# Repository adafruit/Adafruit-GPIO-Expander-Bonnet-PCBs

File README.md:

## Adafruit GPIO Expander Bonnet PCB

<a href="http://www.adafruit.com/products/4132"><br/>
Click here to purchase one from the Adafruit shop</a>

PCB files for the Adafruit GPIO Expander Bonnet. Format is EagleCAD schematic and board layout
* https://www.adafruit.com/product/4132

### Description

The Raspberry Pi is an amazing single board computer - and one of the best parts is that GPIO connector! 40 pins of digital goodness you can twiddle to control LEDs, sensors, buttons, radios, displays - just about any device you can imagine. This Adafruit GPIO Expander Bonnet will give you even more digital deliciousness - 16 more digital input/output pins are yours for any desire you have. The outputs are grouped into two 16-pin connectors that have a matching ground pin. You can set each pin to be a digital output (high or low) or as an input, with an internal pull-up if you like!

Simply pop the Bonnet on top of your Pi, the circuitry connects to the SDA/SCL I2C pins for control. The MCP23017 chip converts our Python commands to pin instructions.

When used as an output, each pin can supply up to 20mA (current clamped) - so you can drive LEDs directly. The datasheet recommends you keep the total current draw to under 125mA for the whole chip. We set up the expander chip for 5V logic by default (the I2C is level shifted so that's 3V logic). We did that so you can drive white, blue or green LEDs that sometimes aren't too happy with 3.3V logic. Or, you can cut/solder a jumper to change it to 3.3V logic.

When used as an input, you can set up a pull-up resistor so buttons and switches don't need extra resistors - just wire the pin to one side and ground to the other! There's interrupt capabilities on the chip, and two IRQ pins (INTA and INTB) you can solder a wire to, if you want to have a quick way of telling if any of the GPIO's changed.

By soldering close the address select jumpers, you can change the address from 0x20 up to 0x27. So, if you wanted to, you could have up to 8 bonnets for 128 total GPIO.

Comes as an assembled and tested Bonnet with slim 2x20 header connector on the bottom. We provide 2 sets of 16-pin IDC sockets, you can solder these in or leave them off for a slim setup. [Follow our guide to use our CircuitPython library with Python 3 for fast and easy setup and configuration, you'll be running in under 5 minutes.](https://learn.adafruit.com/gpio-expander-bonnet/overview)

<b>As of October 31, 2023</b> - We've added an on-board Stemma QT port for easy plug-n-play of I2C sensors and devices. The board also now comes with the two IDC socket headers pre-soldered. Lastly, we've also updated it with Adafruit Pinguin to make a lovely and legible silkscreen

### License

Adafruit invests time and resources providing this open source design, please support Adafruit and open-source hardware by purchasing products from [Adafruit](https://www.adafruit.com)!

Designed by Limor Fried/Ladyada for Adafruit Industries.

Creative Commons Attribution/Share-Alike, all text above must be included in any redistribution. See license.txt for additional details.

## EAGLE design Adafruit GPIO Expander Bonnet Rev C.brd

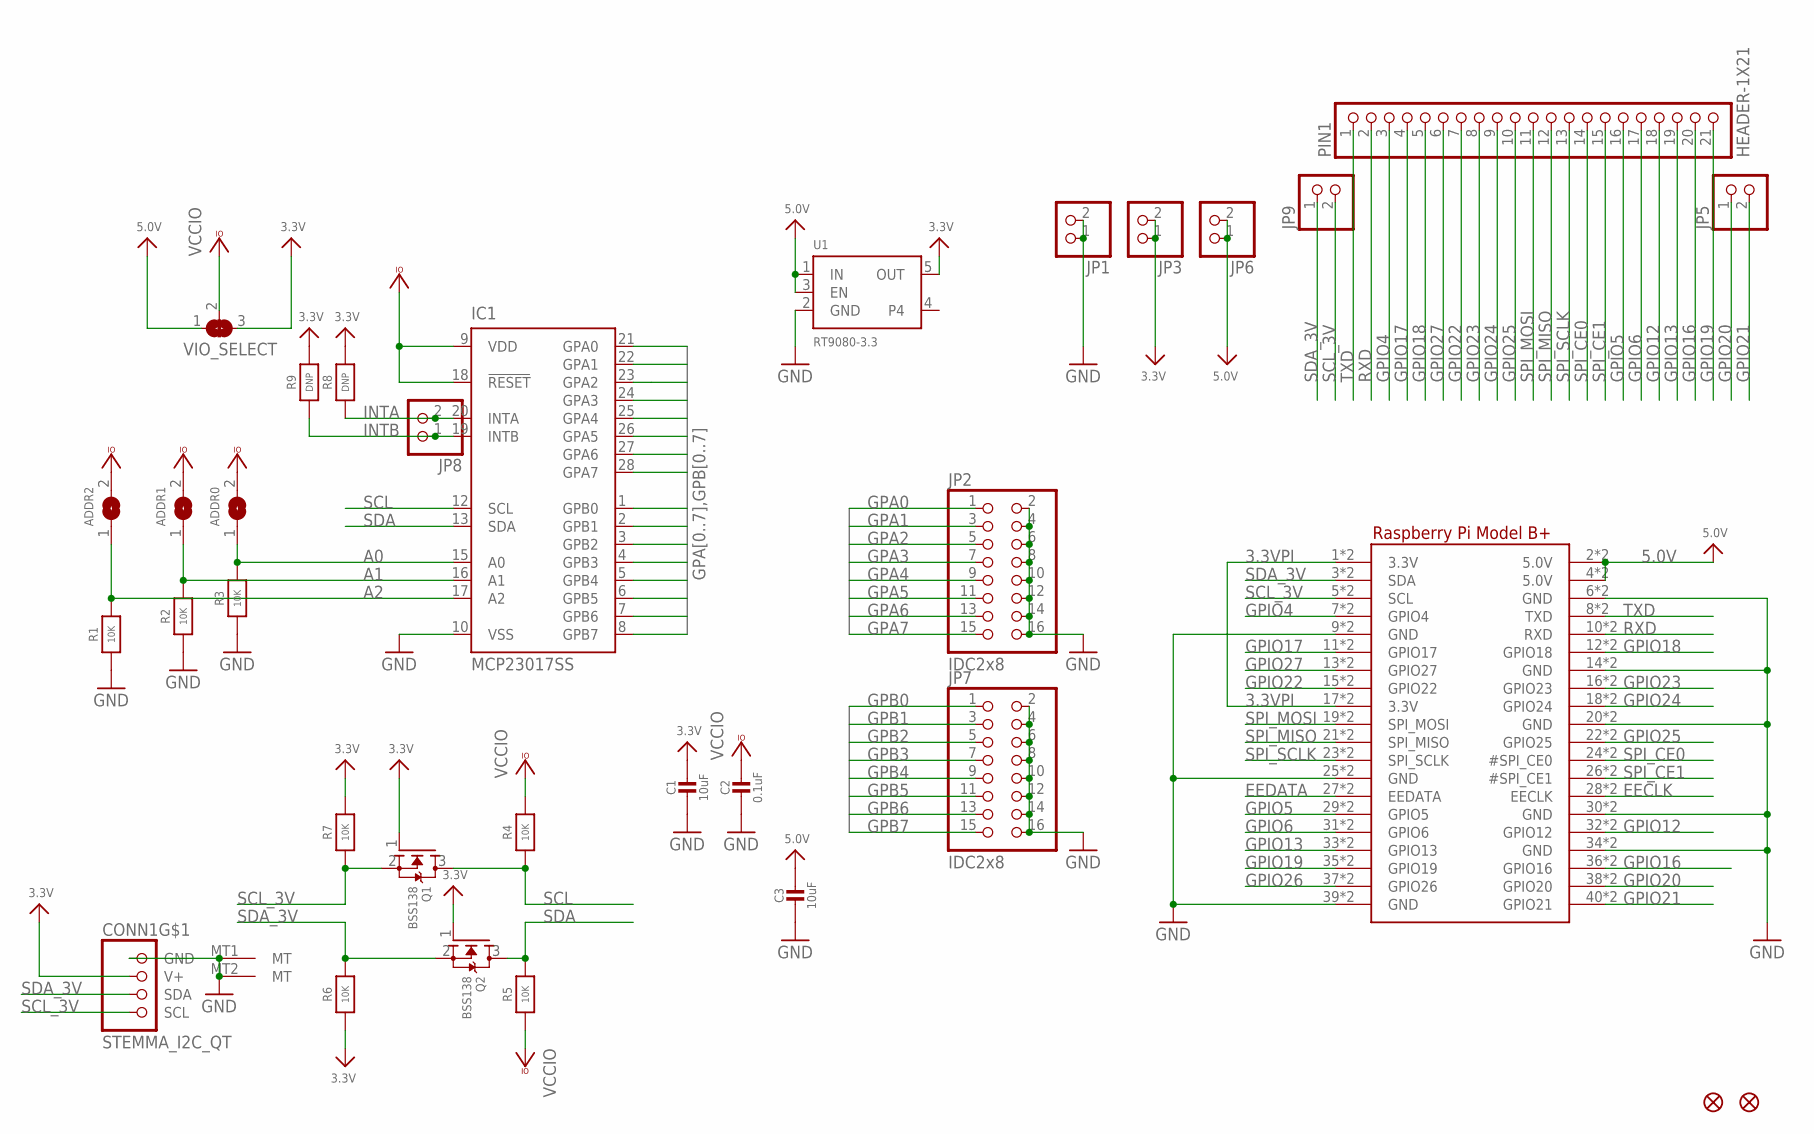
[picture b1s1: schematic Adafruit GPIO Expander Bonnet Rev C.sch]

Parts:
ADDR0, ADDR1, ADDR2: SOLDERJUMPER; SOLDERJUMPER_ARROW_NOPASTE
C1, C3: 10uF; 0805-NO
C2: 0.1uF; 0603-NO
CONN1: STEMMA_I2C_QT; JST_SH4
FID1, FID2: FIDUCIAL_1MM
IC1: MCP23017SS; SSOP28
JP1, JP3, JP5, JP6, JP8, JP9: HEADER-1X2ROUND; 1X02_ROUND
JP2, JP7: IDC2x8; 2X08_SHROUDED
PIN1: HEADER-1X21; 1X21_ROUND_70MIL
Q1, Q2: BSS138; SOT23-WIDE
R1, R2, R3, R4, R5, R6, R7: 10K; 0603-NO
R8, R9: DNP; 0603-NO
RPI1: RASPBERRYPI_BPLUS_BONNET_THMSMT; PI_BONNET_THMSMT
U1: RT9080-3.3; SOT23-5; JLC_ROTATION 0
VIO_SELECT: SOLDERJUMPER_2WAY; SOLDERJUMPER_2WAY_OPEN_NOPASTE

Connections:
3.3V: C1.1, CONN1.2 (V+), JP3.1, JP3.2, Q1.1 (G), Q2.1 (G), R6.1, R7.2, R8.2, R9.2, U1.5 (OUT), VIO_SELECT.3
3.3VPI: RPI1.1 (3.3V), RPI1.17 (3.3V), RPI1.S1 (3.3V), RPI1.S17 (3.3V)
5.0V: C3.1, JP6.1, JP6.2, RPI1.2 (5.0V), RPI1.4 (5.0V), RPI1.S2 (5.0V), RPI1.S4 (5.0V), U1.1 (IN), U1.3 (EN), VIO_SELECT.1
A0: ADDR0.1, IC1.15 (A0), R3.2
A1: ADDR1.1, IC1.16 (A1), R2.2
A2: ADDR2.1, IC1.17 (A2), R1.2
EECLK: RPI1.28 (EECLK), RPI1.S28 (EECLK)
EEDATA: RPI1.27 (EEDATA), RPI1.S27 (EEDATA)
GND: C1.2, C2.2, C3.2, CONN1.1 (GND), CONN1.MT1 (MT), CONN1.MT2 (MT), IC1.10 (VSS), JP1.1, JP1.2, JP2.2, JP2.4, JP2.6, JP2.8, JP2.10, JP2.12, JP2.14, JP2.16, JP7.2, JP7.4, JP7.6, JP7.8, JP7.10, JP7.12, JP7.14, JP7.16, R1.1, R2.1, R3.1, RPI1.6 (GND), RPI1.9 (GND), RPI1.14 (GND), RPI1.20 (GND), RPI1.25 (GND), RPI1.30 (GND), RPI1.34 (GND), RPI1.39 (GND), RPI1.S6 (GND), RPI1.S9 (GND), RPI1.S14 (GND), RPI1.S20 (GND), RPI1.S25 (GND), RPI1.S30 (GND), RPI1.S34 (GND), RPI1.S39 (GND), U1.2 (GND)
GPA0: IC1.21 (GPA0), JP2.1
GPA1: IC1.22 (GPA1), JP2.3
GPA2: IC1.23 (GPA2), JP2.5
GPA3: IC1.24 (GPA3), JP2.7
GPA4: IC1.25 (GPA4), JP2.9
GPA5: IC1.26 (GPA5), JP2.11
GPA6: IC1.27 (GPA6), JP2.13
GPA7: IC1.28 (GPA7), JP2.15
GPB0: IC1.1 (GPB0), JP7.1
GPB1: IC1.2 (GPB1), JP7.3
GPB2: IC1.3 (GPB2), JP7.5
GPB3: IC1.4 (GPB3), JP7.7
GPB4: IC1.5 (GPB4), JP7.9
GPB5: IC1.6 (GPB5), JP7.11
GPB6: IC1.7 (GPB6), JP7.13
GPB7: IC1.8 (GPB7), JP7.15
GPIO4: PIN1.3, RPI1.7 (GPIO4), RPI1.S7 (GPIO4)
GPIO5: PIN1.16, RPI1.29 (GPIO5), RPI1.S29 (GPIO5)
GPIO6: PIN1.17, RPI1.31 (GPIO6), RPI1.S31 (GPIO6)
GPIO12: PIN1.18, RPI1.32 (GPIO12), RPI1.S32 (GPIO12)
GPIO13: PIN1.19, RPI1.33 (GPIO13), RPI1.S33 (GPIO13)
GPIO16: PIN1.20, RPI1.36 (GPIO16), RPI1.S36 (GPIO16)
GPIO17: PIN1.4, RPI1.11 (GPIO17), RPI1.S11 (GPIO17)
GPIO18: PIN1.5, RPI1.12 (GPIO18), RPI1.S12 (GPIO18)
GPIO19: PIN1.21, RPI1.35 (GPIO19), RPI1.S35 (GPIO19)
GPIO20: JP5.1, RPI1.38 (GPIO20), RPI1.S38 (GPIO20)
GPIO21: JP5.2, RPI1.40 (GPIO21), RPI1.S40 (GPIO21)
GPIO22: PIN1.7, RPI1.15 (GPIO22), RPI1.S15 (GPIO22)
GPIO23: PIN1.8, RPI1.16 (GPIO23), RPI1.S16 (GPIO23)
GPIO24: PIN1.9, RPI1.18 (GPIO24), RPI1.S18 (GPIO24)
GPIO25: PIN1.10, RPI1.22 (GPIO25), RPI1.S22 (GPIO25)
GPIO26: RPI1.37 (GPIO26), RPI1.S37 (GPIO26)
GPIO27: PIN1.6, RPI1.13 (GPIO27), RPI1.S13 (GPIO27)
INTA: IC1.20 (INTA), JP8.2, R8.1
INTB: IC1.19 (INTB), JP8.1, R9.1
RXD: PIN1.2, RPI1.10 (RXD), RPI1.S10 (RXD)
SCL: IC1.12 (SCL), Q1.3 (D), R4.1
SCL_3V: CONN1.4 (SCL), JP9.2, Q1.2 (S), R7.1, RPI1.5 (SCL), RPI1.S5 (SCL)
SDA: IC1.13 (SDA), Q2.3 (D), R5.2
SDA_3V: CONN1.3 (SDA), JP9.1, Q2.2 (S), R6.2, RPI1.3 (SDA), RPI1.S3 (SDA)
SPI_CE0: PIN1.14, RPI1.24 (#SPI_CE0), RPI1.S24 (#SPI_CE0)
SPI_CE1: PIN1.15, RPI1.26 (#SPI_CE1), RPI1.S26 (#SPI_CE1)
SPI_MISO: PIN1.12, RPI1.21 (SPI_MISO), RPI1.S21 (SPI_MISO)
SPI_MOSI: PIN1.11, RPI1.19 (SPI_MOSI), RPI1.S19 (SPI_MOSI)
SPI_SCLK: PIN1.13, RPI1.23 (SPI_SCLK), RPI1.S23 (SPI_SCLK)
TXD: PIN1.1, RPI1.8 (TXD), RPI1.S8 (TXD)
VCCIO: ADDR0.2, ADDR1.2, ADDR2.2, C2.1, IC1.9 (VDD), IC1.18 (!RESET), R4.2, R5.1, VIO_SELECT.2

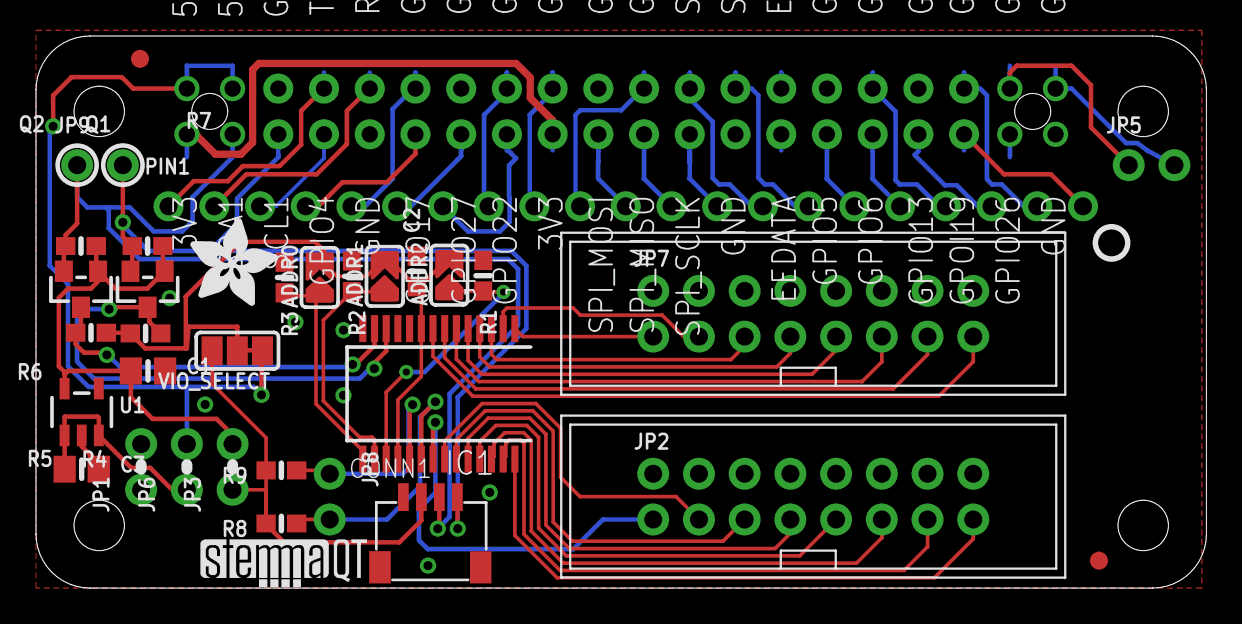
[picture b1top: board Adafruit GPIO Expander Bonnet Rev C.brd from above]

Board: 2 copper layers, 65.0 x 30.7 mm, 100 parts (0 on the bottom side), 56 nets.

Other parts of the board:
PLABEL0: PLABEL0
PLABEL1: PLABEL1
PLABEL2: PLABEL2
PLABEL3: PLABEL3
PLABEL4: PLABEL4
PLABEL5: PLABEL5
PLABEL6: PLABEL6
PLABEL7: PLABEL7
PLABEL8: PLABEL8
PLABEL9: PLABEL9
PLABEL10: PLABEL10
PLABEL11: PLABEL11
PLABEL12: PLABEL12
PLABEL13: PLABEL13
PLABEL14: PLABEL14
PLABEL15: PLABEL15
PLABEL16: PLABEL16
PLABEL17: PLABEL17
PLABEL18: PLABEL18
PLABEL19: PLABEL19
PLABEL20: PLABEL20
PLABEL21: PLABEL21
PLABEL22: PLABEL22
PLABEL23: PLABEL23
PLABEL24: PLABEL24
PLABEL25: PLABEL25
PLABEL26: PLABEL26
PLABEL27: PLABEL27
PLABEL28: PLABEL28
PLABEL29: PLABEL29
PLABEL30: PLABEL30
PLABEL31: PLABEL31
PLABEL32: PLABEL32
PLABEL33: PLABEL33
PLABEL34: PLABEL34
PLABEL35: PLABEL35
PLABEL36: PLABEL36
PLABEL37: PLABEL37
PLABEL38: PLABEL38
PLABEL39: PLABEL39
PLABEL40: PLABEL40
PLABEL41: PLABEL41
PLABEL42: PLABEL42
PLABEL43: PLABEL43
PLABEL44: PLABEL44
PLABEL45: PLABEL45
PLABEL46: PLABEL46
PLABEL47: PLABEL47
PLABEL48: PLABEL48
PLABEL49: PLABEL49
PLABEL50: PLABEL50
PLABEL51: PLABEL51
PLABEL52: PLABEL52
PLABEL53: PLABEL53
PLABEL54: PLABEL54
PLABEL55: PLABEL55
PLABEL56: PLABEL56
PLABEL57: PLABEL57
PLABEL58: PLABEL58
PLABEL59: PLABEL59
PLABEL60: PLABEL60
PLABEL61: PLABEL61
PLABEL62: PLABEL62
PLABEL63: PLABEL63
U$12: ADAFRUIT_5MM
U$13: PCBFEAT-REV-040
U$19: STEMMAQT

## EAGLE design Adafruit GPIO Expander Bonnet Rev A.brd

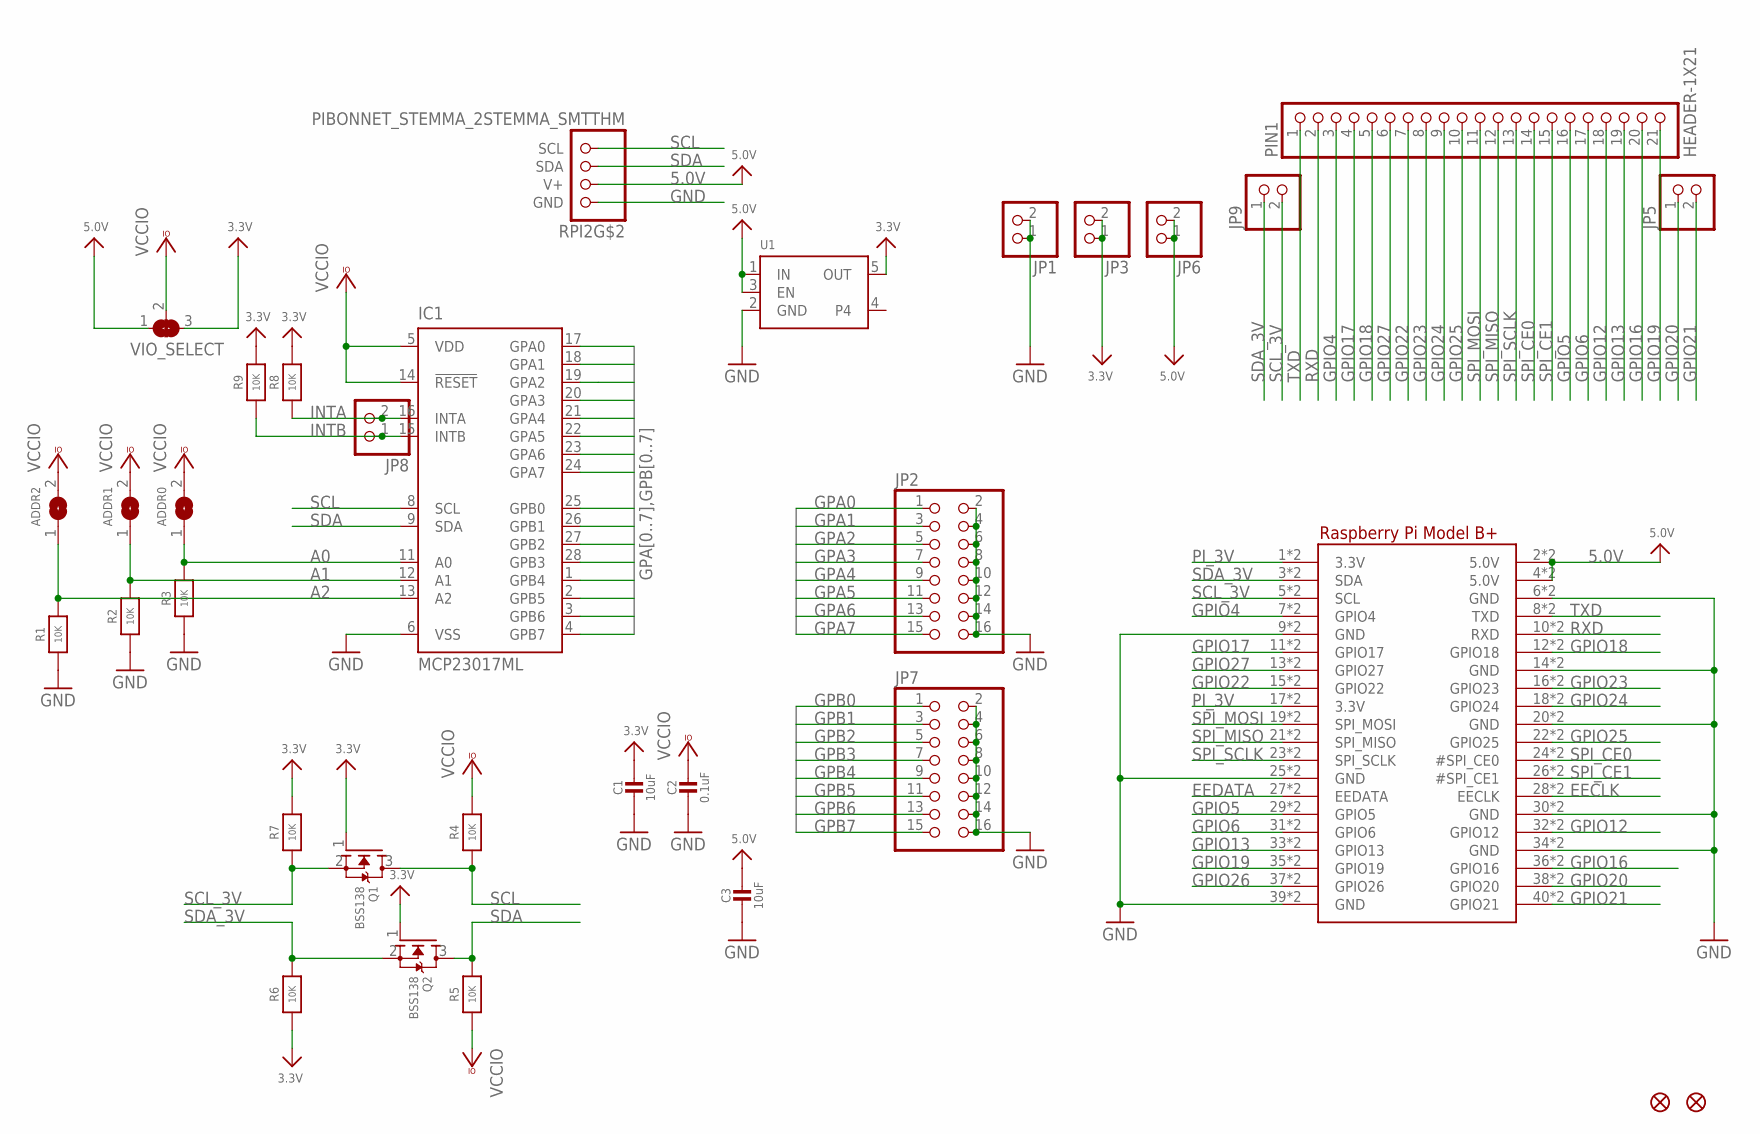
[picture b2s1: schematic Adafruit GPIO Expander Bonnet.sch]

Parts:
ADDR0, ADDR1, ADDR2: SOLDERJUMPER; SOLDERJUMPER_ARROW_NOPASTE
C1, C3: 10uF; 0805-NO
C2: 0.1uF; 0603-NO
FID1, FID2: FIDUCIAL_1MM
IC1: MCP23017ML; QFN28-ML_6X6MM
JP1, JP3, JP5, JP6, JP8, JP9: HEADER-1X2ROUND; 1X02_ROUND
JP2, JP7: HEADER-2X8_SHROUDED; 2X08_SHROUDED
PIN1: HEADER-1X21; 1X21_ROUND_70MIL
Q1, Q2: BSS138; SOT23-WIDE
R1, R2, R3, R4, R5, R6, R7, R8, R9: 10K; 0603-NO
RPI2: PIBONNET_STEMMA_2STEMMA_SMTTHM; PI_BONNET_2STEMMA_SMT
U1: VREG_SOT23-5; SOT23-5
VIO_SELECT: SOLDERJUMPER_2WAY; SOLDERJUMPER_2WAY_OPEN_NOPASTE

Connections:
3.3V: C1.1, JP3.1, JP3.2, Q1.1 (G), Q2.1 (G), R6.1, R7.2, R8.2, R9.2, U1.5 (OUT), VIO_SELECT.3
5.0V: C3.1, JP6.1, JP6.2, RPI2.2 (5.0V), RPI2.4 (5.0V), RPI2.S2 (5.0V), RPI2.S4 (5.0V), RPI2.V+, RPI2.V+1 (V+), U1.1 (IN), U1.3 (EN), VIO_SELECT.1
A0: ADDR0.1, IC1.11 (A0), R3.2
A1: ADDR1.1, IC1.12 (A1), R2.2
A2: ADDR2.1, IC1.13 (A2), R1.2
EECLK: RPI2.28 (EECLK), RPI2.S28 (EECLK)
EEDATA: RPI2.27 (EEDATA), RPI2.S27 (EEDATA)
GND: C1.2, C2.2, C3.2, IC1.6 (VSS), JP1.1, JP1.2, JP2.2, JP2.4, JP2.6, JP2.8, JP2.10, JP2.12, JP2.14, JP2.16, JP7.2, JP7.4, JP7.6, JP7.8, JP7.10, JP7.12, JP7.14, JP7.16, R1.1, R2.1, R3.1, RPI2.6 (GND), RPI2.9 (GND), RPI2.14 (GND), RPI2.20 (GND), RPI2.25 (GND), RPI2.30 (GND), RPI2.34 (GND), RPI2.39 (GND), RPI2.GND, RPI2.GND1 (GND), RPI2.S6 (GND), RPI2.S9 (GND), RPI2.S14 (GND), RPI2.S20 (GND), RPI2.S25 (GND), RPI2.S30 (GND), RPI2.S34 (GND), RPI2.S39 (GND), U1.2 (GND)
GPA0: IC1.17 (GPA0), JP2.1
GPA1: IC1.18 (GPA1), JP2.3
GPA2: IC1.19 (GPA2), JP2.5
GPA3: IC1.20 (GPA3), JP2.7
GPA4: IC1.21 (GPA4), JP2.9
GPA5: IC1.22 (GPA5), JP2.11
GPA6: IC1.23 (GPA6), JP2.13
GPA7: IC1.24 (GPA7), JP2.15
GPB0: IC1.25 (GPB0), JP7.1
GPB1: IC1.26 (GPB1), JP7.3
GPB2: IC1.27 (GPB2), JP7.5
GPB3: IC1.28 (GPB3), JP7.7
GPB4: IC1.1 (GPB4), JP7.9
GPB5: IC1.2 (GPB5), JP7.11
GPB6: IC1.3 (GPB6), JP7.13
GPB7: IC1.4 (GPB7), JP7.15
GPIO4: PIN1.3, RPI2.7 (GPIO4), RPI2.S7 (GPIO4)
GPIO5: PIN1.16, RPI2.29 (GPIO5), RPI2.S29 (GPIO5)
GPIO6: PIN1.17, RPI2.31 (GPIO6), RPI2.S31 (GPIO6)
GPIO12: PIN1.18, RPI2.32 (GPIO12), RPI2.S32 (GPIO12)
GPIO13: PIN1.19, RPI2.33 (GPIO13), RPI2.S33 (GPIO13)
GPIO16: PIN1.20, RPI2.36 (GPIO16), RPI2.S36 (GPIO16)
GPIO17: PIN1.4, RPI2.11 (GPIO17), RPI2.S11 (GPIO17)
GPIO18: PIN1.5, RPI2.12 (GPIO18), RPI2.S12 (GPIO18)
GPIO19: PIN1.21, RPI2.35 (GPIO19), RPI2.S35 (GPIO19)
GPIO20: JP5.1, RPI2.38 (GPIO20), RPI2.S38 (GPIO20)
GPIO21: JP5.2, RPI2.40 (GPIO21), RPI2.S40 (GPIO21)
GPIO22: PIN1.7, RPI2.15 (GPIO22), RPI2.S15 (GPIO22)
GPIO23: PIN1.8, RPI2.16 (GPIO23), RPI2.S16 (GPIO23)
GPIO24: PIN1.9, RPI2.18 (GPIO24), RPI2.S18 (GPIO24)
GPIO25: PIN1.10, RPI2.22 (GPIO25), RPI2.S22 (GPIO25)
GPIO26: RPI2.37 (GPIO26), RPI2.S37 (GPIO26)
GPIO27: PIN1.6, RPI2.13 (GPIO27), RPI2.S13 (GPIO27)
INTA: IC1.16 (INTA), JP8.2, R8.1
INTB: IC1.15 (INTB), JP8.1, R9.1
PI_3V: RPI2.1 (3.3V), RPI2.17 (3.3V), RPI2.S1 (3.3V), RPI2.S17 (3.3V)
RXD: PIN1.2, RPI2.10 (RXD), RPI2.S10 (RXD)
SCL: IC1.8 (SCL), Q1.3 (D), R4.1, RPI2.SCL, RPI2.SCL1 (SCL)
SCL_3V: JP9.2, Q1.2 (S), R7.1, RPI2.5 (SCL), RPI2.S5 (SCL)
SDA: IC1.9 (SDA), Q2.3 (D), R5.2, RPI2.SDA, RPI2.SDA1 (SDA)
SDA_3V: JP9.1, Q2.2 (S), R6.2, RPI2.3 (SDA), RPI2.S3 (SDA)
SPI_CE0: PIN1.14, RPI2.24 (#SPI_CE0), RPI2.S24 (#SPI_CE0)
SPI_CE1: PIN1.15, RPI2.26 (#SPI_CE1), RPI2.S26 (#SPI_CE1)
SPI_MISO: PIN1.12, RPI2.21 (SPI_MISO), RPI2.S21 (SPI_MISO)
SPI_MOSI: PIN1.11, RPI2.19 (SPI_MOSI), RPI2.S19 (SPI_MOSI)
SPI_SCLK: PIN1.13, RPI2.23 (SPI_SCLK), RPI2.S23 (SPI_SCLK)
TXD: PIN1.1, RPI2.8 (TXD), RPI2.S8 (TXD)
VCCIO: ADDR0.2, ADDR1.2, ADDR2.2, C2.1, IC1.5 (VDD), IC1.14 (!RESET), R4.2, R5.1, VIO_SELECT.2

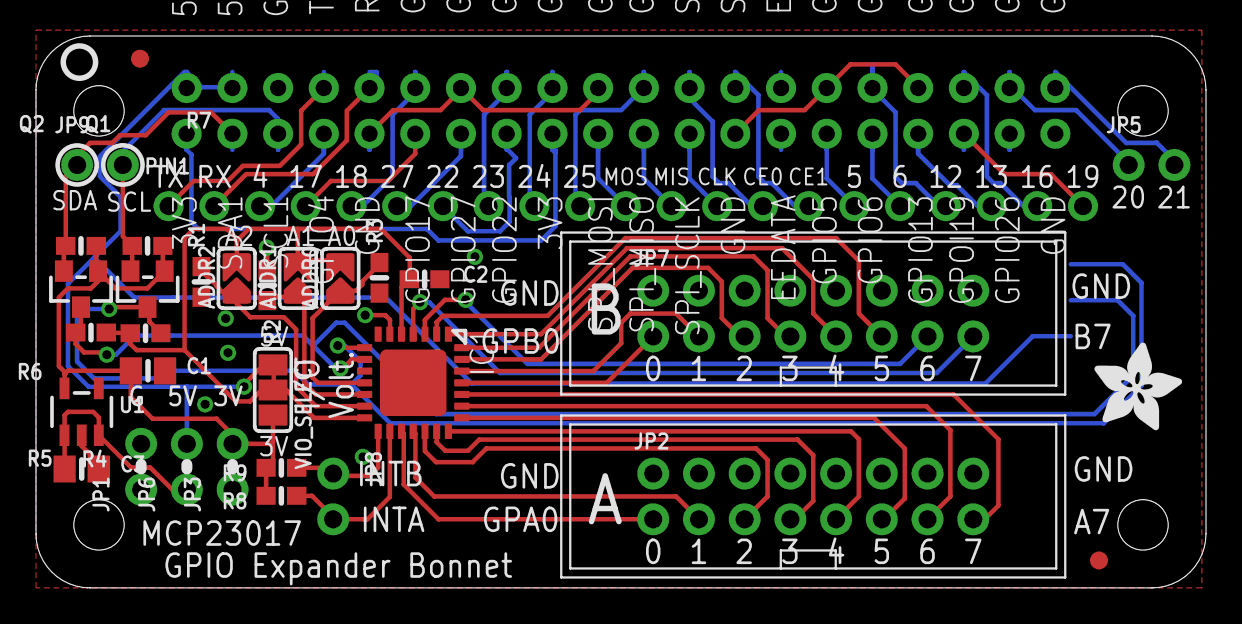
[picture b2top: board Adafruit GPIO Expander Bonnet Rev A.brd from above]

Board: 2 copper layers, 65.0 x 30.7 mm, 34 parts (0 on the bottom side), 56 nets.

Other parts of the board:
U$12: ADAFRUIT_5MM
U$13: PCBFEAT-REV-040

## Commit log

2019-03-05 adding board files
2019-07-17 updated to use cookiecutter for pcb repos
2023-11-02 updating for rev C

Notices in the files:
parts and their libraries:
microbuilder: This work is placed in the public domain, and may be freely used for commercial and non-commercial work with the following conditions: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
